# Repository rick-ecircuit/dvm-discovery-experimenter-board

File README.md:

# DVM Discovery Board
## Intro
The DVM Discovery Board allows students, engineers and DIYers to quickly build and learn key voltage measuring concepts and circuits. Hands-on prototyping and experimenting boosts understanding and intuition!

* Easy-to-use Experimenter Board.
* Circuit Options
	* 1 to 3 Customizable Voltage Ranges
	* Unipolar (+ input only) or Bipolar (+ / - input)
	* Precision Mode (Vref option)
	* Range Select: Manual Push-button or Auto 
* Simple interface to the Arduino UNO (or other MicroController).
* C Code Examples - run, modify, expand!
* Excel Design Calculator - gains, RC values, resolution, settling time.

## Flexible Hands-On Learning
* Quickly build and explore multiple measurement options. 
* Solderless headers for easy component changes.

## Building Blocks
Start with the basic circuit blocks
* Input Divider (2 Ranges)
* Low-Pass Filter
* Push-Button

Add blocks to expand your project
* Amplifier (additional range)
* Negative Rail (bipolar input)
* Voltage Reference (precision mode).

## Micro-Controller & C Code
* Easily interfaces to a MicroController Bd like the Arduino UNO.
* Run the code for the Basic or Advanced Voltmeter. Modify or customize for your project.
	* Basic ( 2-Range, Unipolar Input ):  DVM_discovery_basic_1.ino
	* Advanced ( 3-Range, Bipolar Input ):  DVM_discovery_3range_bipolar_1.ino

## User's Guide
* Description, Schematics, BOM
* Design and analysis equations
* DVM Examples: Basic and Advanced

## KiCAD Files
The schematic and PCB were created with KiCad, a free and open-source software suite that provides a complete EDA toolset including schematic capture, PCB layout, 3D visualization. https://www.kicad.org/

## Open-Source Project
The DVM Discovery is Open Source - anyone can inspect, make, modify and distribute the project.
Download PDFs and KiCAD PCB files (schematic, PCB, etc.).

## Excel Op Amp Design Calculator
An Excel Toolkit of Calculations created for hands-on experimenting. Apply, modify or customize as needed!
* Input Divider & Amplifier 
* Low-Pass Filter 
* Scale & Shift Network
* ADC Conversion and Resolution

<br>Let me know what you find helpful or any other comments and suggestions. Thanks!  
www.ecircuitcenter.com/contact.htm

Have fun on your next learning / design / coding adventure!

Rick  
eCircuit Center  
https://ecircuitcenter.com/

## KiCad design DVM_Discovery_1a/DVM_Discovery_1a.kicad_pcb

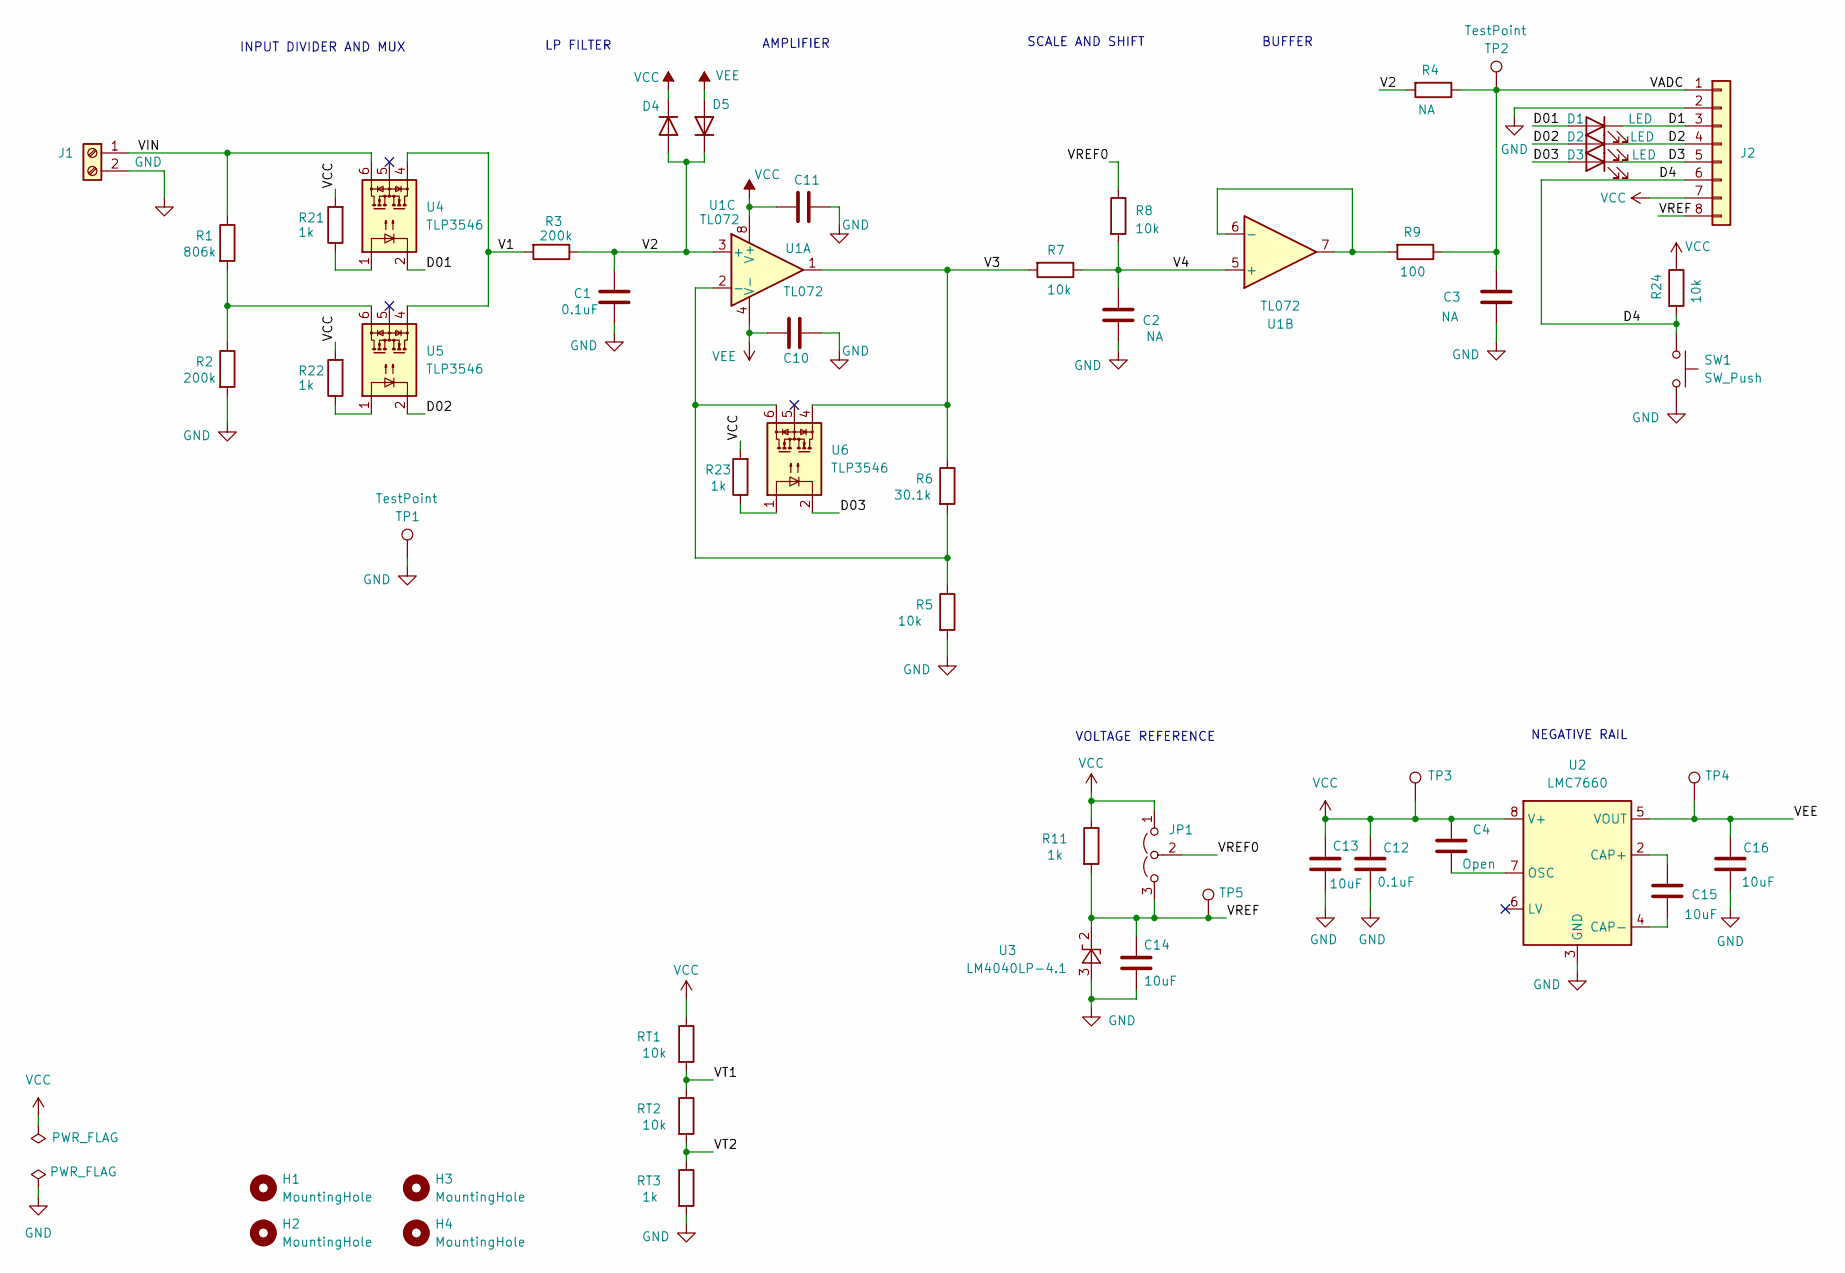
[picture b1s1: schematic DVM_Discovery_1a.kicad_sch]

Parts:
C1, C10, C11, C12: 0.1uF; C_Disc_D3.0mm_W1.6mm_P2.50mm_wider_center_dia
C2, C3: NA; C_Disc_D3.0mm_W1.6mm_P2.50mm_wider_center_dia
C4: Open; C_Disc_D3.0mm_W1.6mm_P2.50mm_wider_center_dia
C13, C14, C15, C16: 10uF; C_Disc_D3.0mm_W1.6mm_P2.50mm_wider_center_dia
D1, D2, D3: LED; LED_D3.0mm
D4, D5: 1N914; D_DO-35_SOD27_P7.62mm_Horizontal
H1, H2, H3, H4: MountingHole; MountingHole_3.7mm
J1: Screw_Terminal_01x02; TerminalBlock_bornier-2_P5.08mm
J2: Conn_01x08; PinSocket_1x08_P2.54mm_Vertical
JP1: Jumper_3_Open; PinHeader_1x03_P2.54mm_Vertical
R1: 806k; R_Axial_DIN0204_L3.6mm_D1.6mm_P7.62mm_Horizontal-bigger_hole
R2, R3: 200k; R_Axial_DIN0204_L3.6mm_D1.6mm_P7.62mm_Horizontal-bigger_hole
R4: NA; R_Axial_DIN0204_L3.6mm_D1.6mm_P7.62mm_Horizontal-bigger_hole
R5, R7, R8, R24: 10k; R_Axial_DIN0204_L3.6mm_D1.6mm_P7.62mm_Horizontal-bigger_hole
R6: 30.1k; R_Axial_DIN0204_L3.6mm_D1.6mm_P7.62mm_Horizontal-bigger_hole
R9: 100; R_Axial_DIN0204_L3.6mm_D1.6mm_P7.62mm_Horizontal-bigger_hole
R11, R21, R22, R23: 1k; R_Axial_DIN0204_L3.6mm_D1.6mm_P7.62mm_Horizontal-bigger_hole
RT1, RT2: 10k; R_Axial_DIN0204_L3.6mm_D1.6mm_P7.62mm_Horizontal-bigger_hole
RT3: 1k; R_Axial_DIN0204_L3.6mm_D1.6mm_P7.62mm_Horizontal-bigger_hole
SW1: SW_Push; SW_TH_Tactile_Omron_B3F-100x
TP1, TP2: TestPoint; TestPoint_Keystone_5005-5009_Compact
TP3, TP4, TP5: TestPoint; TestPoint_THTPad_D2.0mm_Drill1.0mm_bigger
U1: TL072; DIP-8_W7.62mm
U2: LMC7660; DIP-8_W7.62mm
U3: LM4040LP-4.1; TO-92_Inline_Wide
U4, U5, U6: TLP3546; DIP-6_W7.62mm

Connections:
/D1: D1.1 (K), J2.3
/D01: D1.2 (A), U4.2
/D2: D2.1 (K), J2.4
/D02: D2.2 (A), U5.2
/D3: D3.1 (K), J2.5
/D03: D3.2 (A), U6.2
/D4: J2.6, R24.2, SW1.1
/V1: R3.2, U4.4, U5.4
/V2: C1.1, D4.2 (A), D5.1 (K), R3.1, R4.2, U1.3 (+)
/V3: R6.1, R7.2, U1.1, U6.4
/V4: C2.1, R7.1, R8.2, U1.5 (+)
/VADC: C3.1, J2.1, R4.1, R9.1, TP2.1
/VIN: J1.1, R1.1, U4.6
/VREF: C14.1, J2.8, JP1.3 (B), R11.2, TP5.1, U3.2 (K)
/VREF0: JP1.2 (C), R8.1
/VT1: RT1.2, RT2.1
/VT2: RT2.2, RT3.1
GND: C1.2, C2.2, C3.2, C10.2, C11.2, C12.2, C13.2, C14.2, C16.2, J1.2, J2.2, R2.2, R5.2, RT3.2, SW1.2, TP1.1, U2.3 (GND), U3.3 (A)
unnamed: R1.2, R2.1, U5.6
unnamed: R21.1, U4.1
unnamed: R22.1, U5.1
unnamed: R23.1, U6.1
unnamed: R5.1, R6.2, U1.2 (-), U6.6
unnamed: R9.2, U1.6 (-), U1.7
unnamed: C15.1, U2.2 (CAP+)
unnamed: C15.2, U2.4 (CAP-)
unnamed: C4.2, U2.7 (OSC)
VCC: C4.1, C11.1, C12.1, C13.1, D4.1 (K), J2.7, JP1.1 (A), R11.1, R21.2, R22.2, R23.2, R24.1, RT1.1, TP3.1, U1.8 (V+), U2.8 (V+)
VEE: C10.1, C16.1, D5.2 (A), TP4.1, U1.4 (V-), U2.5 (VOUT)

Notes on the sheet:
LP FILTER
AMPLIFIER
BUFFER
SCALE AND SHIFT
NEGATIVE RAIL
INPUT DIVIDER AND MUX
VOLTAGE REFERENCE

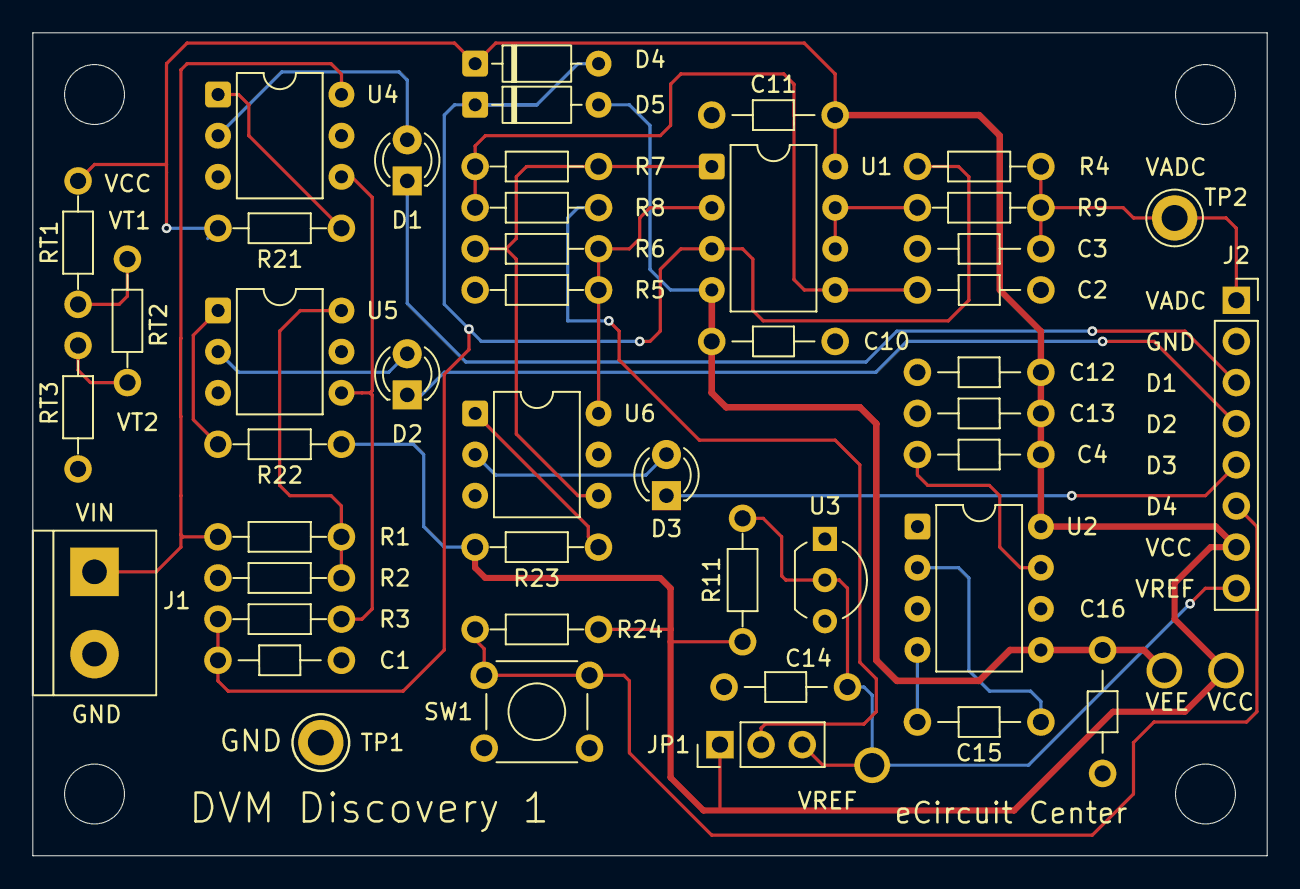
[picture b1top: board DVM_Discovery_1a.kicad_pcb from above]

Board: 2 copper layers, 76.2 x 50.8 mm, 52 parts (0 on the bottom side), 29 nets.

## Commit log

2026-04-06 add user guide, kicad files
2026-04-06 add Arduino code
2026-04-07 update User's Guide
2026-04-09 update users guide
    add applications
